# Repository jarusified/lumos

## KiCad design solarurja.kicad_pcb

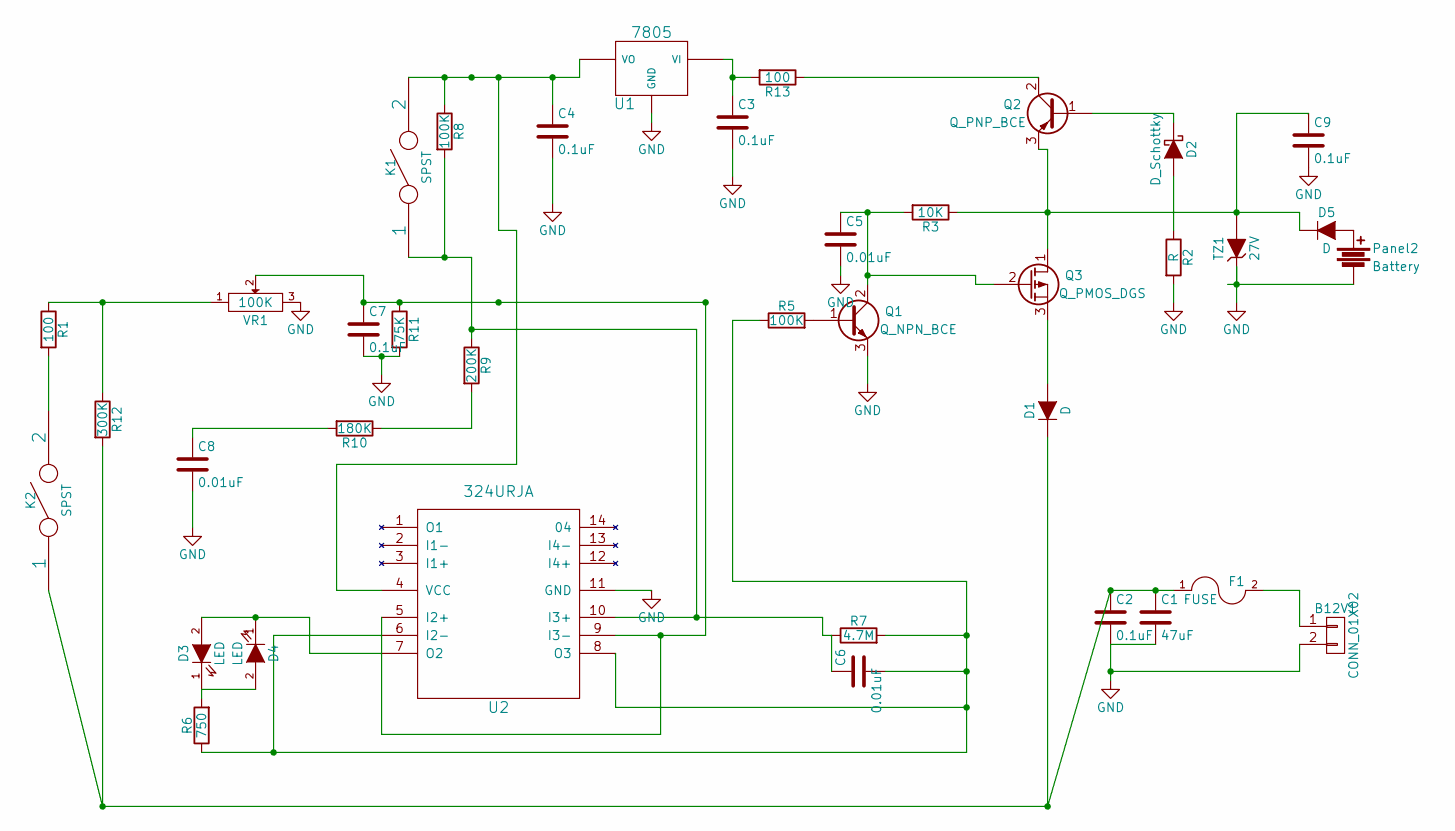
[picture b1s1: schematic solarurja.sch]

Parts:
B12V1: CONN_01X02; Pin_Header_Straight_1x02
C1: 47uF; C_Disc_D3_P2.5
C2, C3, C4, C7, C9: 0.1uF; C_Disc_D3_P2.5
C5, C6, C8: 0.01uF; C_Disc_D3_P2.5
D1, D5: D; D3
D2: D_Schottky; D3
D3, D4: LED; LED-5MM
F1: FUSE; BladeFuse-Mini
K1, K2: SPST; Diode_DO-35_SOD27_Horizontal_RM10
Panel2: Battery; C2V10
Q1: Q_NPN_BCE; TO-92_Inline_Narrow_Oval
Q2: Q_PNP_BCE; TO-92_Inline_Narrow_Oval
Q3: Q_PMOS_DGS; TO-92_Inline_Narrow_Oval
R1, R13: 100; R1
R2: R; R1
R3: 10K; R1
R5, R8: 100K; R1
R6: 750; R1
R7: 4.7M; R1
R9: 200K; R1
R10: 180K; R1
R11: 75K; R1
R12: 300K; R1
TZ1: 27V; SMB_Handsoldering
U1: 7805; 78xx_with_heatsink-78XXH
U2: 324URJA; SSOP-14
VR1: 100K; TO-220_Neutral123_Vertical

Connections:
GND: B12V1.2, C1.2, C2.2, C3.2, C4.2, C5.2, C7.2, C8.2, C9.2, Panel2.2, Q1.3 (E), R2.2, R11.2, TZ1.1 (K), U1.GND, U2.11 (GND), VR1.3
unnamed: B12V1.1, F1.2
unnamed: C1.1, C2.1, D1.1 (K), F1.1, K2.1, R12.2
unnamed: C3.1, R13.2, U1.VI
unnamed: C4.1, K1.2, R8.1, U1.VO, U2.4 (VCC)
unnamed: C5.1, Q1.2 (C), Q3.2 (G), R3.2
unnamed: C6.1, K1.1, R7.1, R8.2, R9.1, U2.10 (I3+)
unnamed: C6.2, R5.1, R6.1, R7.2, U2.6 (I2-), U2.8 (O3)
unnamed: C7.1, R11.1, U2.5 (I2+), U2.9 (I3-), VR1.2
unnamed: C8.1, R10.2
unnamed: C9.1, D5.1 (K), Q2.3 (E), Q3.1 (D), R3.1, TZ1.2 (A)
unnamed: D1.2 (A), Q3.3 (S)
unnamed: D2.1 (K), Q2.1 (B)
unnamed: D2.2 (A), R2.1
unnamed: D3.1 (K), D4.2 (A), R6.2
unnamed: D3.2 (A), D4.1 (K), U2.7 (O2)
unnamed: D5.2 (A), Panel2.1
unnamed: K2.2, R1.2
unnamed: Q1.1 (B), R5.2
unnamed: Q2.2 (C), R13.1
unnamed: R1.1, R12.1, VR1.1
unnamed: R9.2, R10.1

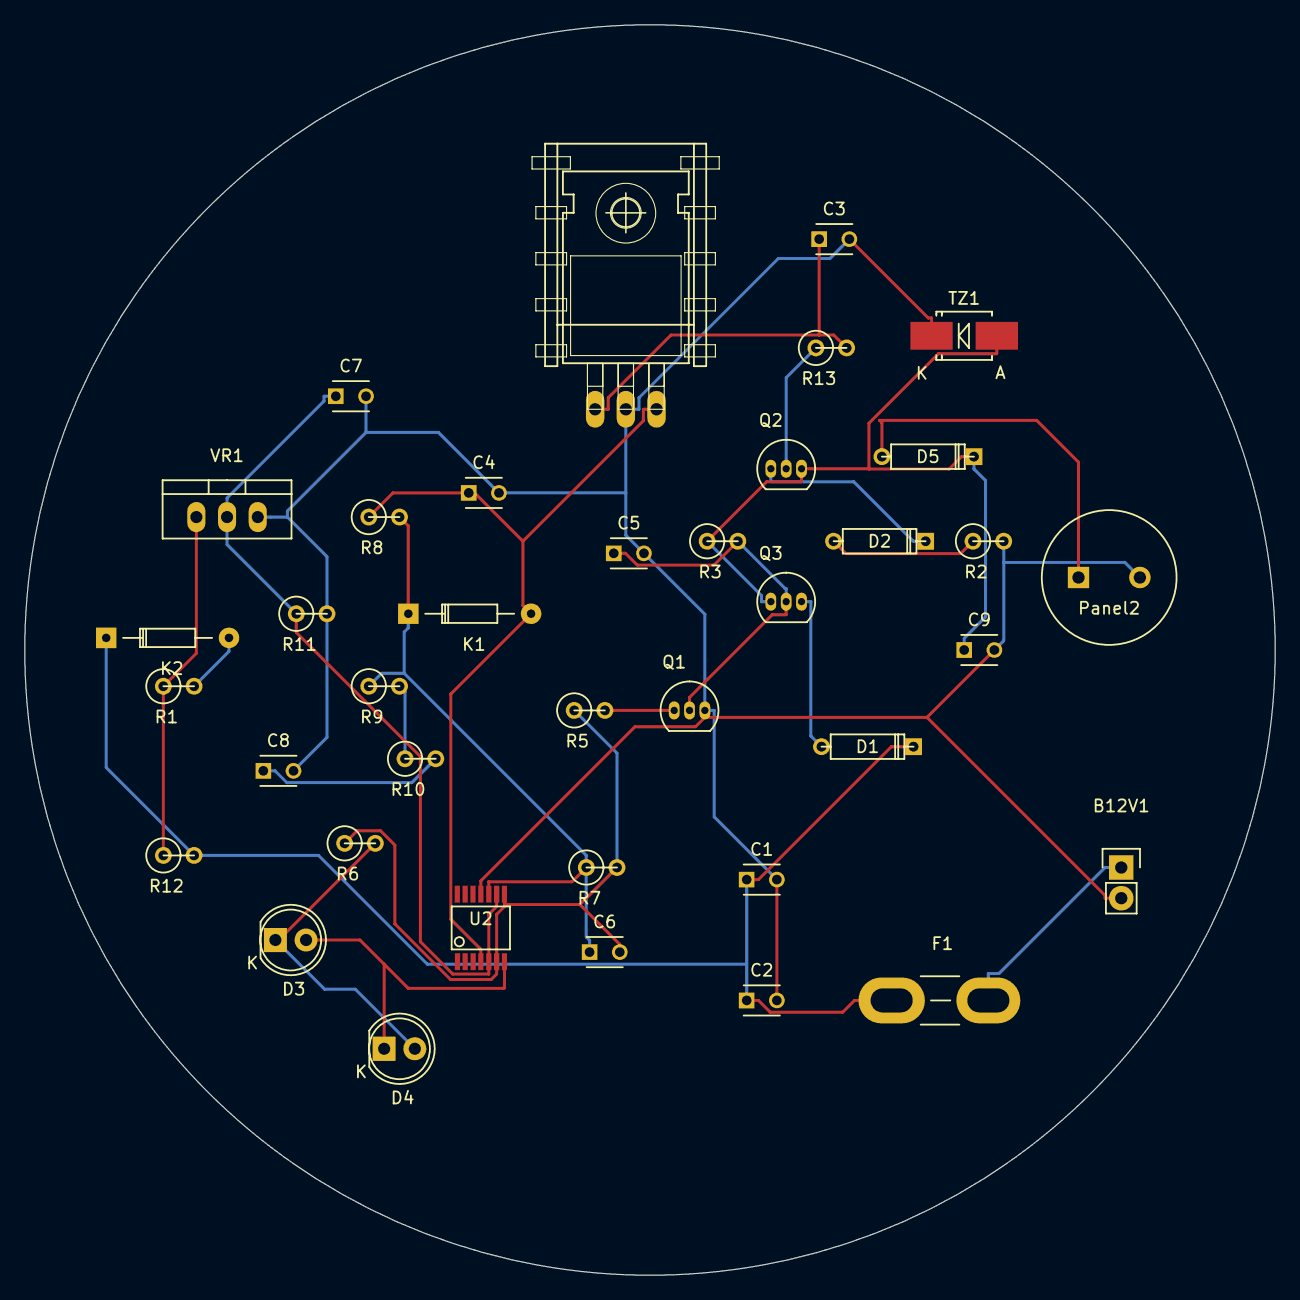
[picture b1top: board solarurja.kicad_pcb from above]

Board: 2 copper layers, 103.5 x 103.5 mm, 38 parts (0 on the bottom side), 22 nets.

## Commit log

2015-11-15 all files included
